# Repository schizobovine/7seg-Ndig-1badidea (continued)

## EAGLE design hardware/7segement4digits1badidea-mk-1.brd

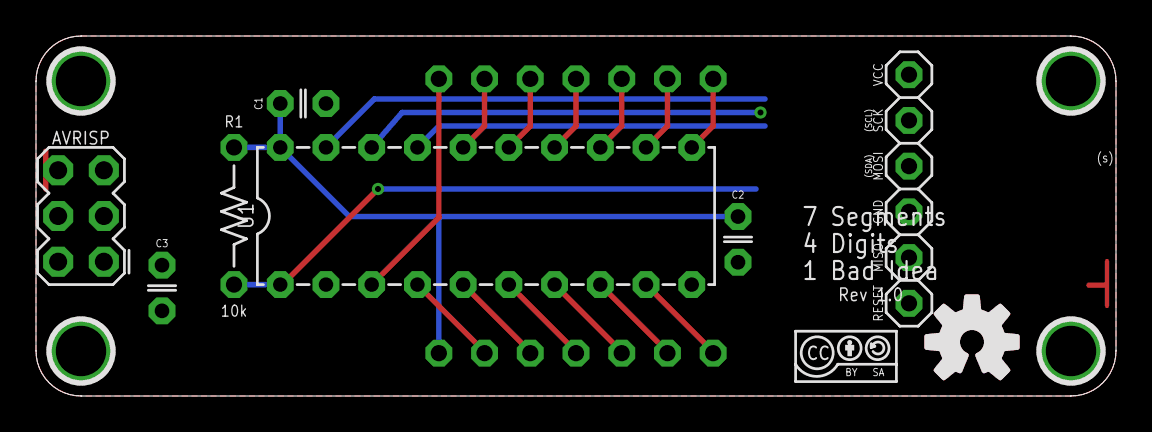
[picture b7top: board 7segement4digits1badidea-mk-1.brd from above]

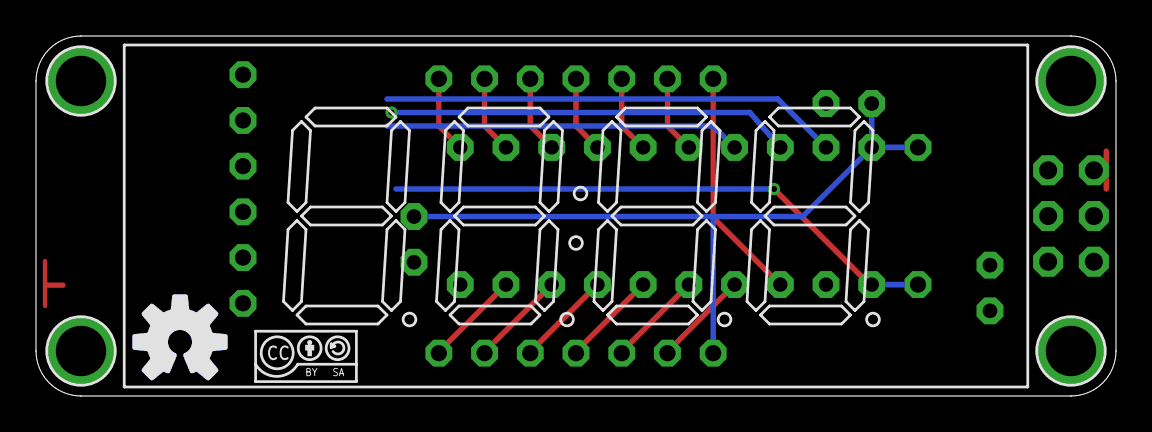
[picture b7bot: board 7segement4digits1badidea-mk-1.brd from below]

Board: 2 copper layers, 60.0 x 20.0 mm, 16 parts (3 on the bottom side), 19 nets.

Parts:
AVRISP: AVR_SPI_PRG_6PTH; 2X3
AVRISP1: AVR_SPI_PRG_6PTH_INLINE_I2C; AVR_ISP_INLINE_PTH_I2C
C1: 0.1uF; C025-024X044
C2: 1uF; C025-024X044
C3: 10uF; C025-024X044
DISPLAY1: 7SED_4DIGIT_14MM14.2MM-CC; 7SEG_4DIG
H1, H2, H3, H4: HOLE#2; HOLE-#2
R1: 10k; RESISTOR-AXIAL-PTH-7.68MM
U1: ATTINY4313; DIL20
U$1, U$2: OSHWLOGO_TOP_0.2_A
U$5, U$6: CC-BY-SA-4.0-NO-URL

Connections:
A: DISPLAY1.P$13, U1.8
B: DISPLAY1.P$9, U1.4
C: DISPLAY1.P$4, U1.14
COLON_K: DISPLAY1.P$7, U1.3
D: DISPLAY1.P$2, U1.12
DIG1: DISPLAY1.P$14, U1.9
DIG2: DISPLAY1.P$11, U1.6
DIG3: DISPLAY1.P$10, U1.5
DIG4: DISPLAY1.P$6, U1.16
DP: DISPLAY1.P$3, U1.13
E: DISPLAY1.P$1, U1.11
F: DISPLAY1.P$12, U1.7
G: DISPLAY1.P$5, U1.15
GND: AVRISP.6, C1.2, C2.2, C3.2, U1.10
MISO: AVRISP.1, U1.18
MOSI/SDA: AVRISP.4, U1.17
RESET: AVRISP.5, R1.P$2, U1.1
SCK/SCL: AVRISP.3, U1.19
VCC: AVRISP.2, C1.1, C2.1, C3.1, DISPLAY1.P$8, R1.P$1, U1.20
